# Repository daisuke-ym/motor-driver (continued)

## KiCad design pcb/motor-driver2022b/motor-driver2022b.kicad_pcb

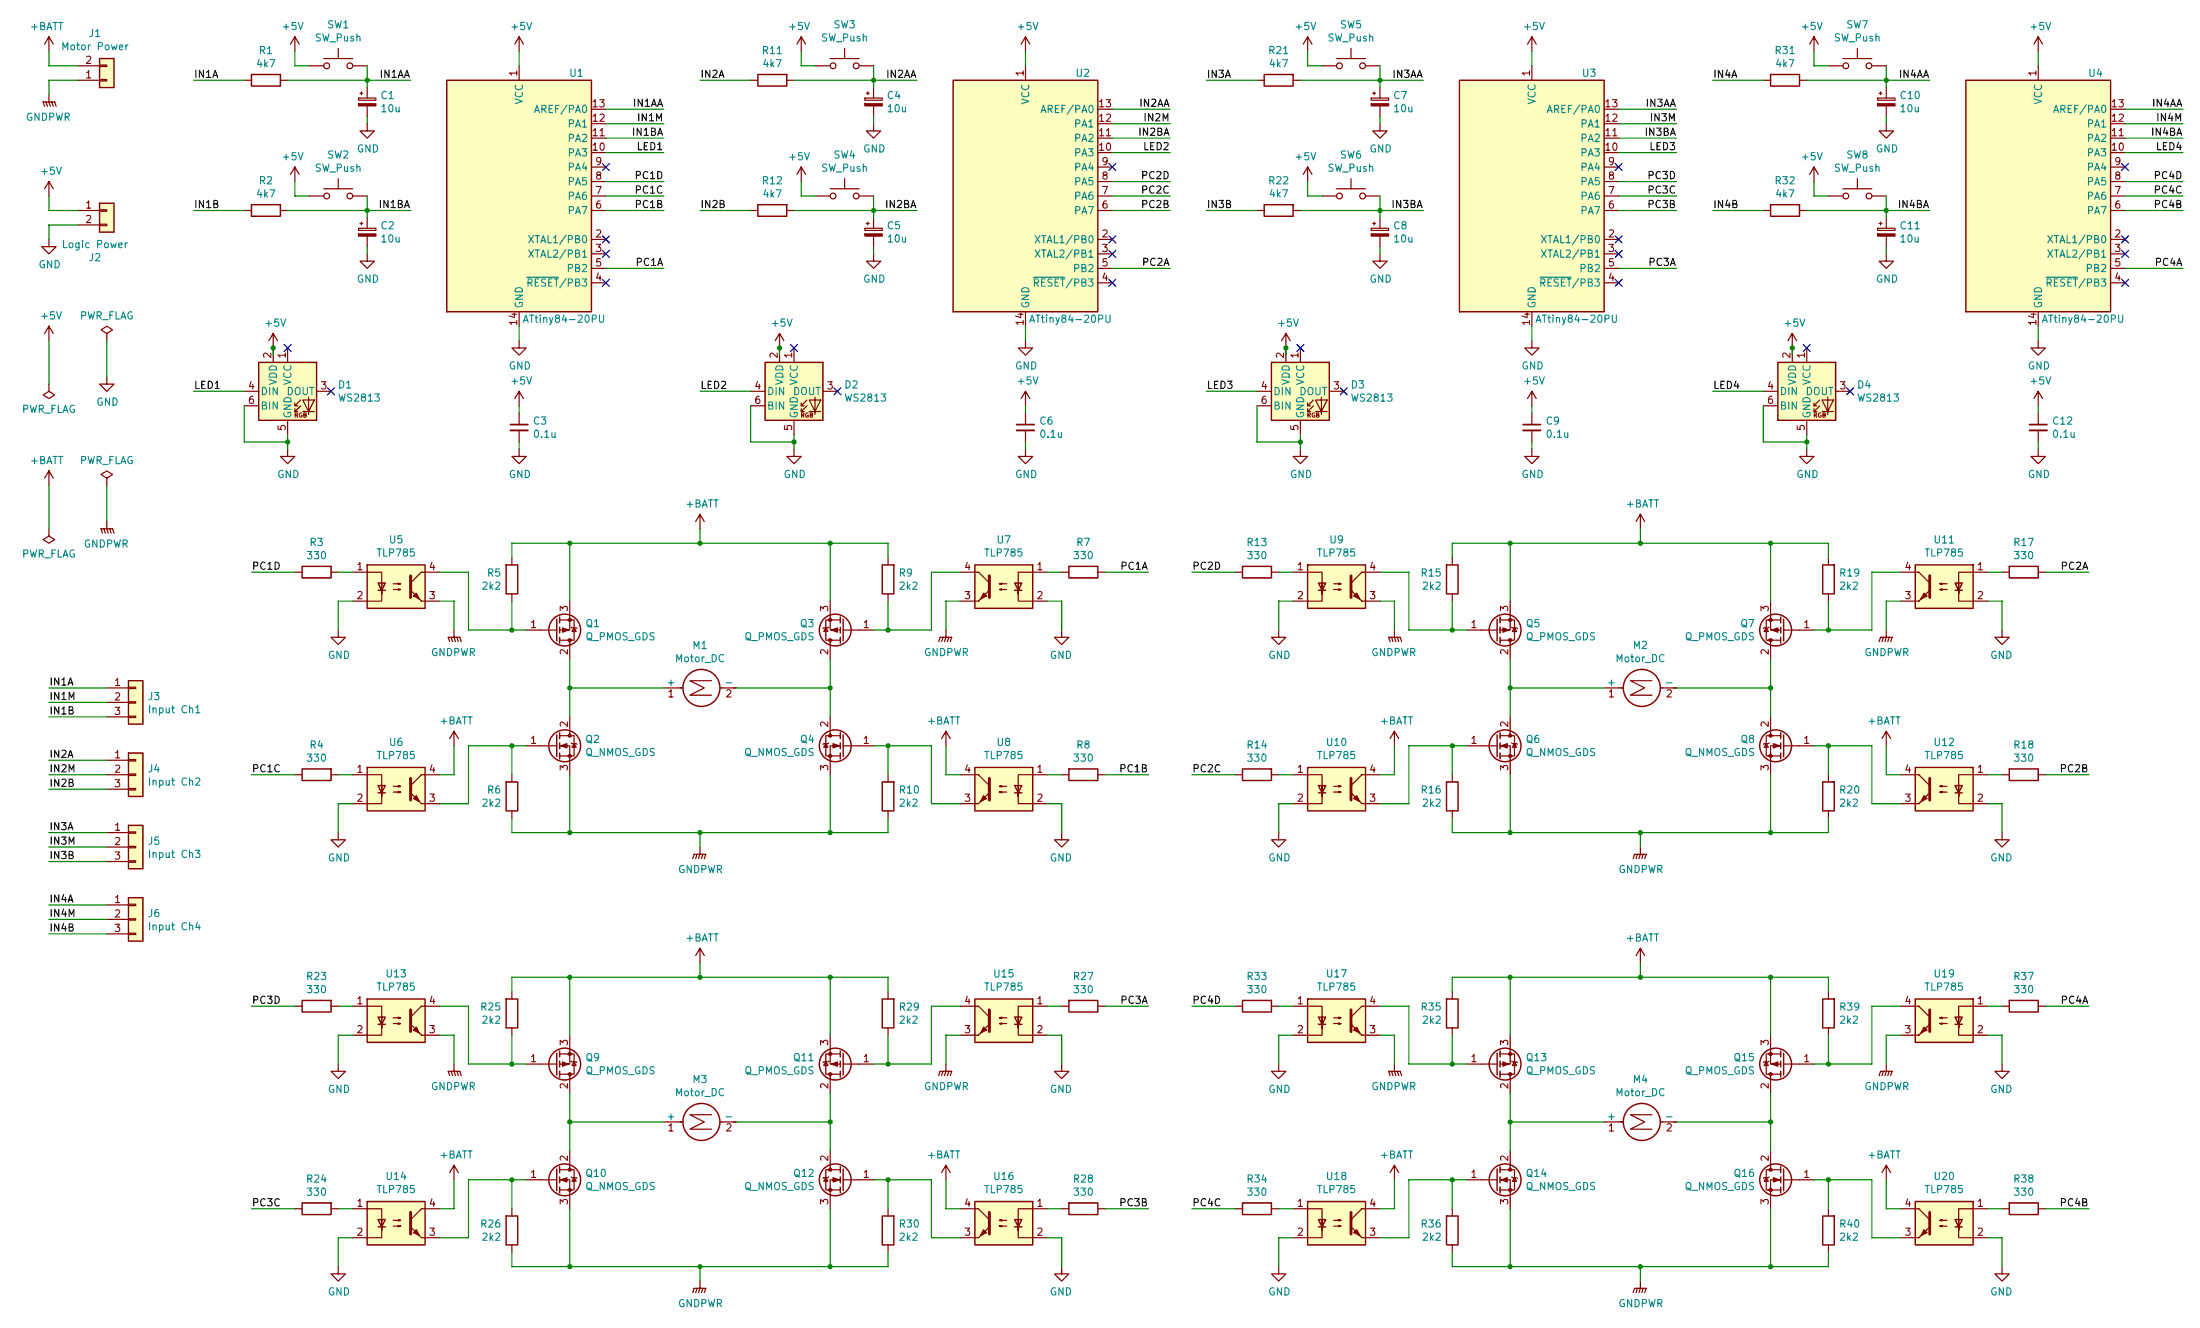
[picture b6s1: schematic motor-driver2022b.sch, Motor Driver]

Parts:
C1, C2, C4, C5, C7, C8, C10, C11: 10u; CP_Radial_D4.0mm_P1.50mm
C3, C6, C9, C12: 0.1u; C_Disc_D3.4mm_W2.1mm_P2.50mm
D1, D2, D3, D4: WS2813; LED_WS2812_PLCC6_5.0x5.0mm_P1.6mm
J1: Motor Power; AMASS_XT30PW-F_1x02_P2.50mm_Horizontal
J2: Logic Power; PinHeader_1x02_P2.54mm_Horizontal
J3: Input Ch1; PinHeader_1x03_P2.54mm_Horizontal
J4: Input Ch2; PinHeader_1x03_P2.54mm_Horizontal
J5: Input Ch3; PinHeader_1x03_P2.54mm_Horizontal
J6: Input Ch4; PinHeader_1x03_P2.54mm_Horizontal
M1, M2, M3, M4: Motor_DC; AMASS_XT30PW-F_1x02_P2.50mm_Horizontal
Q1, Q3, Q5, Q7, Q9, Q11, Q13, Q15: Q_PMOS_GDS; TO-220-3_Horizontal_TabDown
Q2, Q4, Q6, Q8, Q10, Q12, Q14, Q16: Q_NMOS_GDS; TO-220-3_Horizontal_TabDown
R1, R2, R11, R12, R21, R22, R31, R32: 4k7; R_Axial_DIN0207_L6.3mm_D2.5mm_P10.16mm_Horizontal
R3, R4, R7, R8, R13, R14, R17, R18, R23, R24, R27, R28, R33, R34, R37, R38: 330; R_Axial_DIN0207_L6.3mm_D2.5mm_P10.16mm_Horizontal
R5, R6, R9, R10, R15, R16, R19, R20, R25, R26, R29, R30, R35, R36, R39, R40: 2k2; R_Axial_DIN0207_L6.3mm_D2.5mm_P10.16mm_Horizontal
SW1, SW2, SW3, SW4, SW5, SW6, SW7, SW8: SW_Push; TactSW_TVBP06_3.5x6.0-ThroughHole
U1, U2, U3, U4: ATtiny84-20PU; DIP-14_W7.62mm
U5, U6, U7, U8, U9, U10, U11, U12, U13, U14, U15, U16, U17, U18, U19, U20: TLP785; DIP-4_W7.62mm

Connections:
+5V: C3.1, C6.1, C9.1, C12.1, D1.2 (VDD), D2.2 (VDD), D3.2 (VDD), D4.2 (VDD), J2.1, SW1.2, SW2.2, SW3.2, SW4.2, SW5.2, SW6.2, SW7.2, SW8.2, U1.1 (VCC), U2.1 (VCC), U3.1 (VCC), U4.1 (VCC)
+BATT: J1.2, Q1.3 (S), Q3.3 (S), Q5.3 (S), Q7.3 (S), Q9.3 (S), Q11.3 (S), Q13.3 (S), Q15.3 (S), R5.2, R9.2, R15.2, R19.2, R25.2, R29.2, R35.2, R39.2, U6.4, U8.4, U10.4, U12.4, U14.4, U16.4, U18.4, U20.4
/IN1A: J3.1, R1.1
/IN1AA: C1.1, R1.2, SW1.1, U1.13 (AREF/PA0)
/IN1B: J3.3, R2.1
/IN1BA: C2.1, R2.2, SW2.1, U1.11 (PA2)
/IN1M: J3.2, U1.12 (PA1)
/IN2A: J4.1, R11.1
/IN2AA: C4.1, R11.2, SW3.1, U2.13 (AREF/PA0)
/IN2B: J4.3, R12.1
/IN2BA: C5.1, R12.2, SW4.1, U2.11 (PA2)
/IN2M: J4.2, U2.12 (PA1)
/IN3A: J5.1, R21.1
/IN3AA: C7.1, R21.2, SW5.1, U3.13 (AREF/PA0)
/IN3B: J5.3, R22.1
/IN3BA: C8.1, R22.2, SW6.1, U3.11 (PA2)
/IN3M: J5.2, U3.12 (PA1)
/IN4A: J6.1, R31.1
/IN4AA: C10.1, R31.2, SW7.1, U4.13 (AREF/PA0)
/IN4B: J6.3, R32.1
/IN4BA: C11.1, R32.2, SW8.1, U4.11 (PA2)
/IN4M: J6.2, U4.12 (PA1)
/LED1: D1.4 (DIN), U1.10 (PA3)
/LED2: D2.4 (DIN), U2.10 (PA3)
/LED3: D3.4 (DIN), U3.10 (PA3)
/LED4: D4.4 (DIN), U4.10 (PA3)
/PC1A: R7.1, U1.5 (PB2)
/PC1B: R8.1, U1.6 (PA7)
/PC1C: R4.1, U1.7 (PA6)
/PC1D: R3.1, U1.8 (PA5)
/PC2A: R17.1, U2.5 (PB2)
/PC2B: R18.1, U2.6 (PA7)
/PC2C: R14.1, U2.7 (PA6)
/PC2D: R13.1, U2.8 (PA5)
/PC3A: R27.1, U3.5 (PB2)
/PC3B: R28.1, U3.6 (PA7)
/PC3C: R24.1, U3.7 (PA6)
/PC3D: R23.1, U3.8 (PA5)
/PC4A: R37.1, U4.5 (PB2)
/PC4B: R38.1, U4.6 (PA7)
/PC4C: R34.1, U4.7 (PA6)
/PC4D: R33.1, U4.8 (PA5)
GND: C1.2, C2.2, C3.2, C4.2, C5.2, C6.2, C7.2, C8.2, C9.2, C10.2, C11.2, C12.2, D1.5 (GND), D1.6 (BIN), D2.5 (GND), D2.6 (BIN), D3.5 (GND), D3.6 (BIN), D4.5 (GND), D4.6 (BIN), J2.2, U1.14 (GND), U2.14 (GND), U3.14 (GND), U4.14 (GND), U5.2, U6.2, U7.2, U8.2, U9.2, U10.2, U11.2, U12.2, U13.2, U14.2, U15.2, U16.2, U17.2, U18.2, U19.2, U20.2
GNDPWR: J1.1, Q2.3 (S), Q4.3 (S), Q6.3 (S), Q8.3 (S), Q10.3 (S), Q12.3 (S), Q14.3 (S), Q16.3 (S), R6.1, R10.1, R16.1, R20.1, R26.1, R30.1, R36.1, R40.1, U5.3, U7.3, U9.3, U11.3, U13.3, U15.3, U17.3, U19.3
unnamed: M1.1 (+), Q1.2 (D), Q2.2 (D)
unnamed: M1.2 (-), Q3.2 (D), Q4.2 (D)
unnamed: M2.1 (+), Q5.2 (D), Q6.2 (D)
unnamed: M2.2 (-), Q7.2 (D), Q8.2 (D)
unnamed: M3.1 (+), Q9.2 (D), Q10.2 (D)
unnamed: M3.2 (-), Q11.2 (D), Q12.2 (D)
unnamed: M4.1 (+), Q13.2 (D), Q14.2 (D)
unnamed: M4.2 (-), Q15.2 (D), Q16.2 (D)
unnamed: Q1.1 (G), R5.1, U5.4
unnamed: Q2.1 (G), R6.2, U6.3
unnamed: Q3.1 (G), R9.1, U7.4
unnamed: Q4.1 (G), R10.2, U8.3
unnamed: Q5.1 (G), R15.1, U9.4
unnamed: Q6.1 (G), R16.2, U10.3
unnamed: Q7.1 (G), R19.1, U11.4
unnamed: Q8.1 (G), R20.2, U12.3
unnamed: Q9.1 (G), R25.1, U13.4
unnamed: Q10.1 (G), R26.2, U14.3
unnamed: Q11.1 (G), R29.1, U15.4
unnamed: Q12.1 (G), R30.2, U16.3
unnamed: Q13.1 (G), R35.1, U17.4
unnamed: Q14.1 (G), R36.2, U18.3
unnamed: Q15.1 (G), R39.1, U19.4
unnamed: Q16.1 (G), R40.2, U20.3
unnamed: R3.2, U5.1
unnamed: R4.2, U6.1
unnamed: R7.2, U7.1
unnamed: R8.2, U8.1
unnamed: R13.2, U9.1
unnamed: R14.2, U10.1
unnamed: R17.2, U11.1
unnamed: R18.2, U12.1
unnamed: R23.2, U13.1
unnamed: R24.2, U14.1
unnamed: R27.2, U15.1
unnamed: R28.2, U16.1
unnamed: R33.2, U17.1
unnamed: R34.2, U18.1
unnamed: R37.2, U19.1
unnamed: R38.2, U20.1

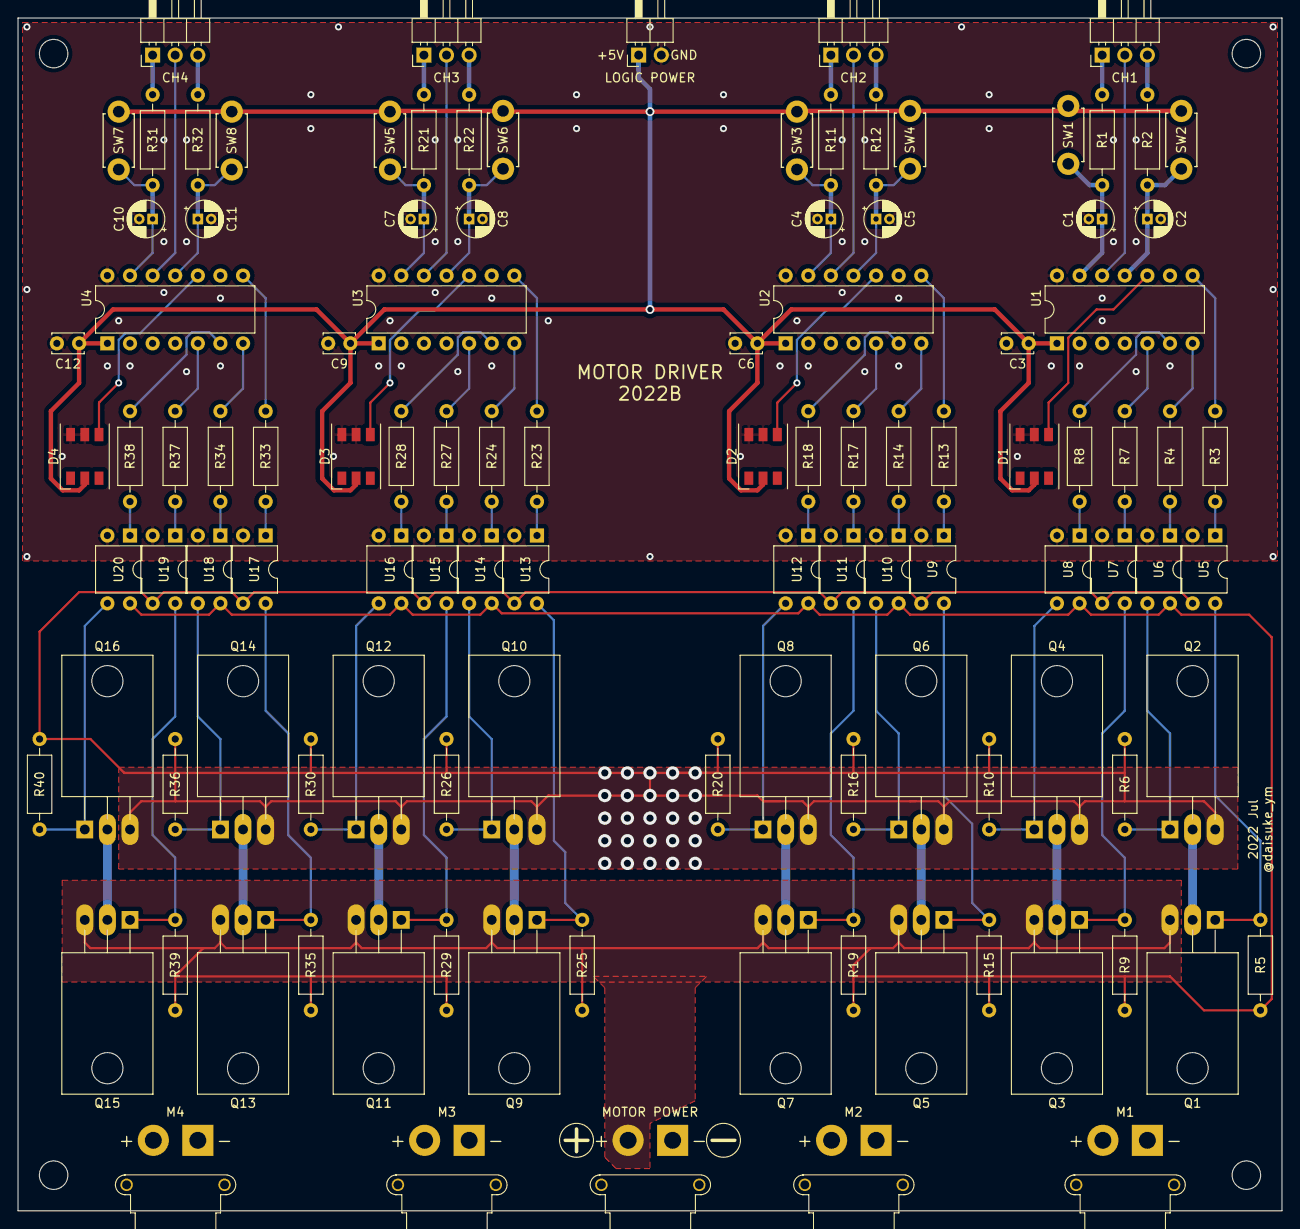
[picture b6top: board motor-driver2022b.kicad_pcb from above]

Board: 2 copper layers, 142.0 x 134.0 mm, 114 parts (0 on the bottom side), 84 nets.

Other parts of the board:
MH1, MH2, MH3, MH4: MountingHole_3.2mm_M3

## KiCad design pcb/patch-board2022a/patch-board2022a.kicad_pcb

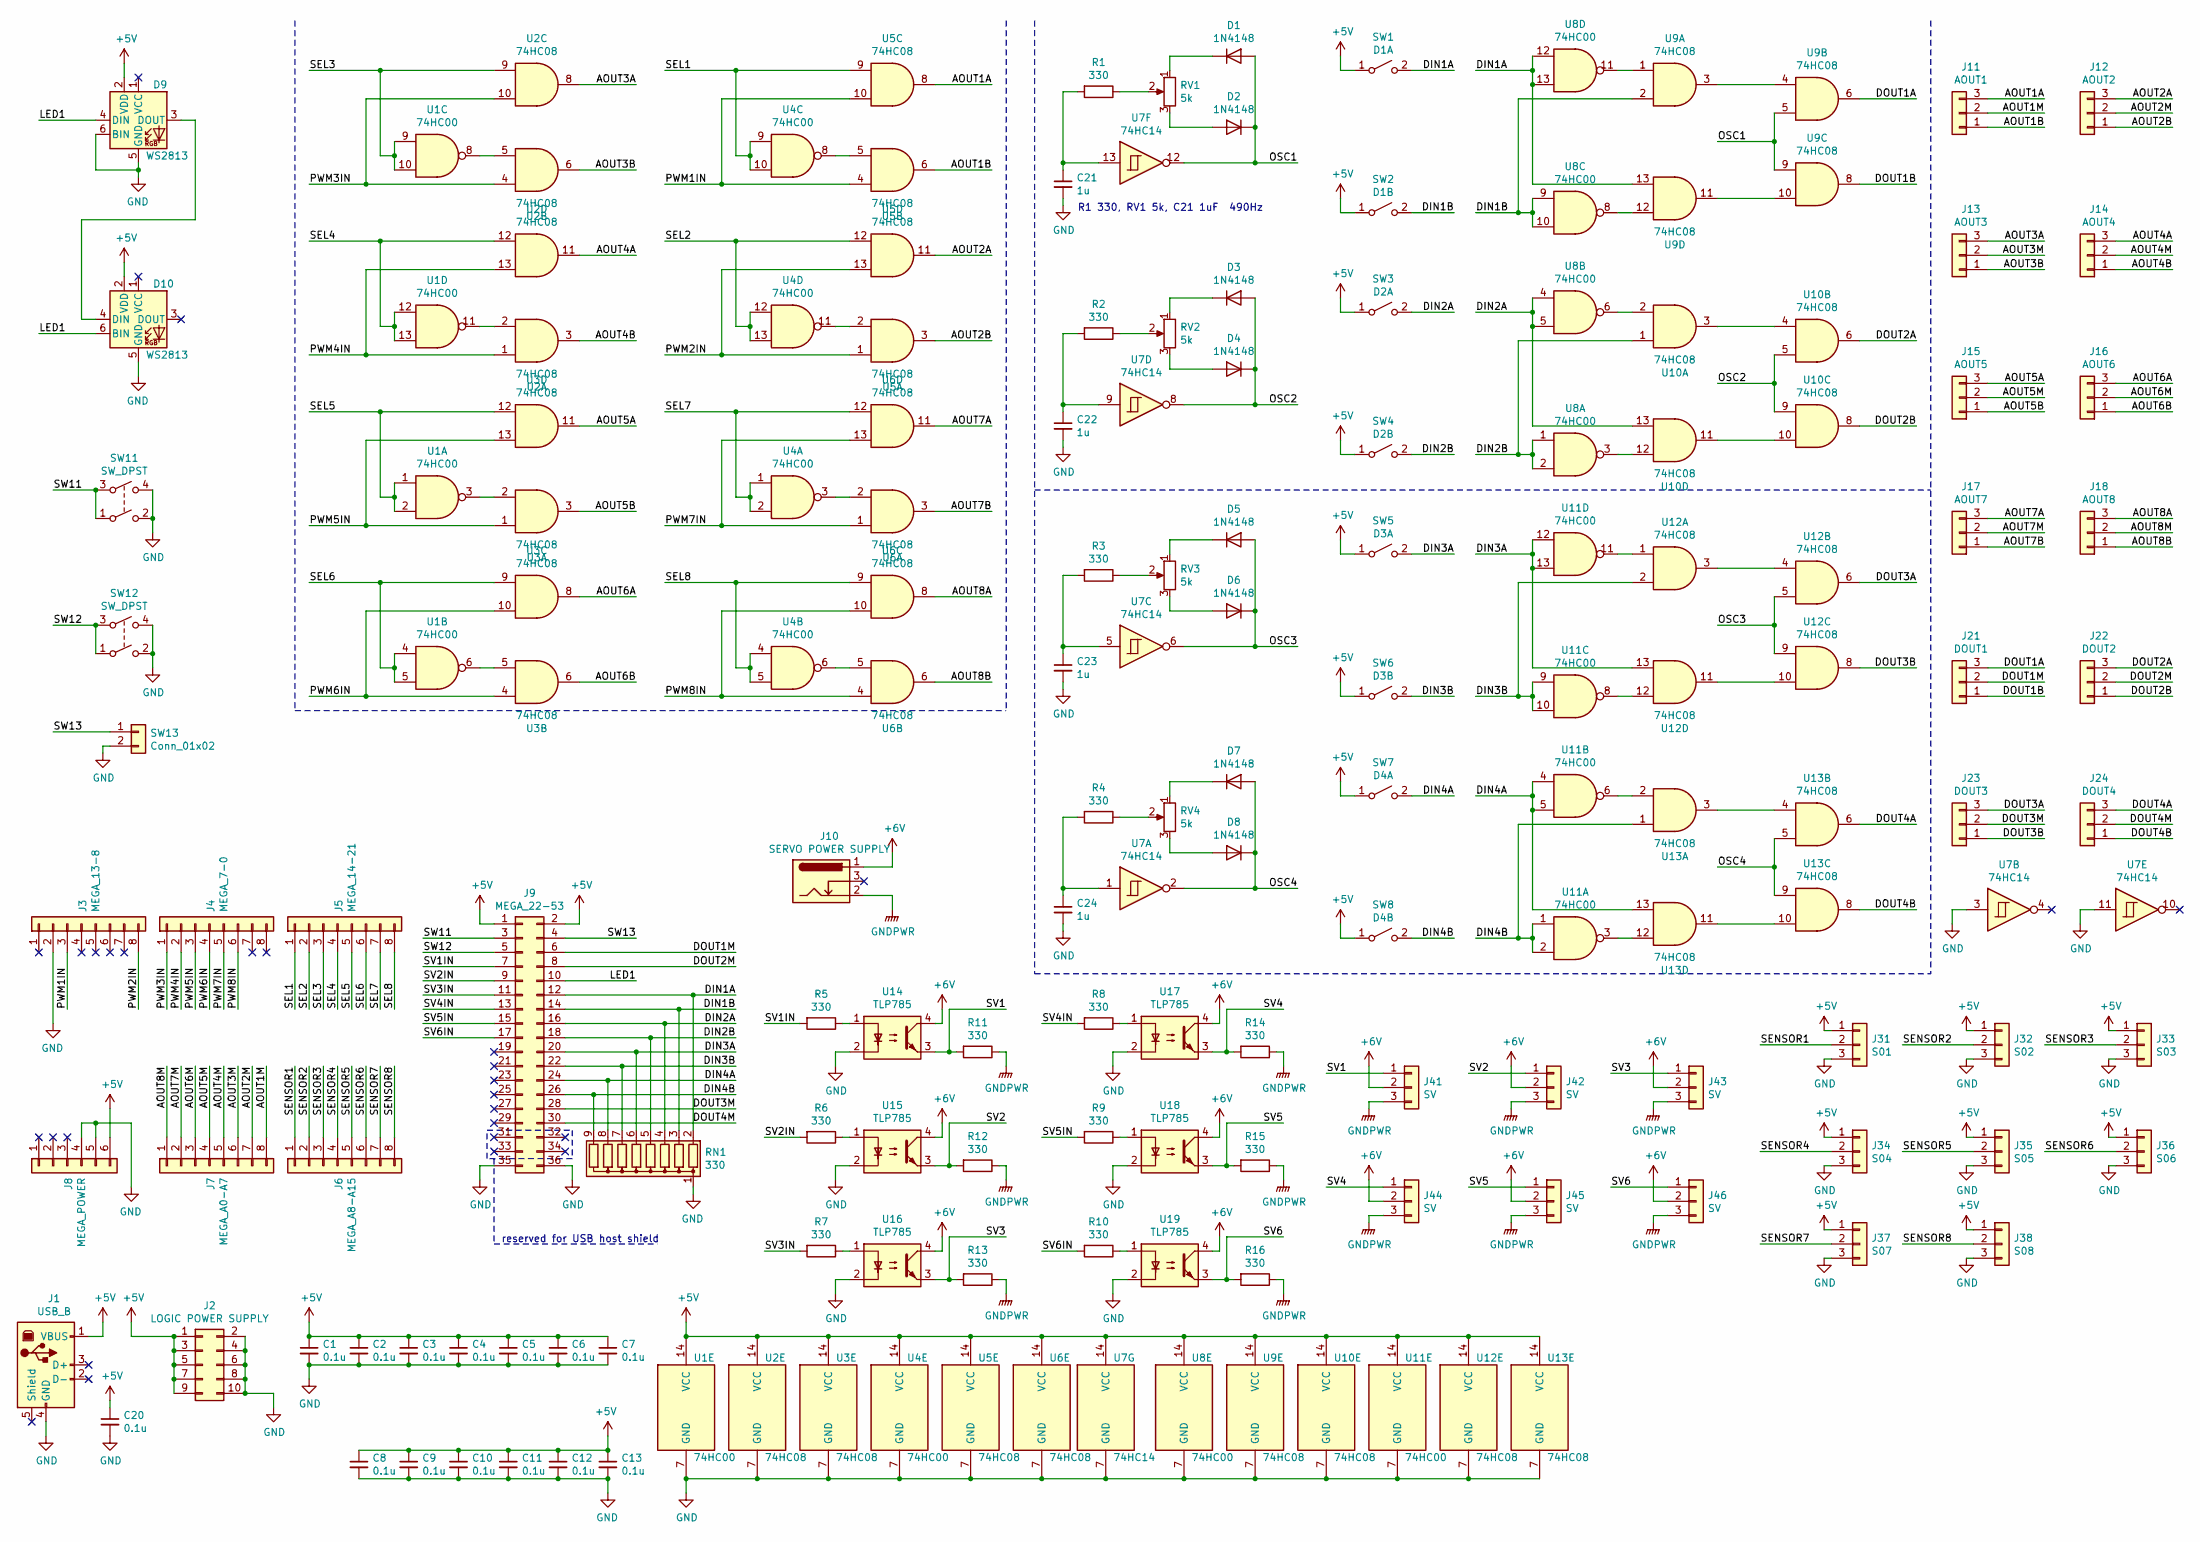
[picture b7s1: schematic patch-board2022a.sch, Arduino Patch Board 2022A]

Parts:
C1, C2, C3, C4, C5, C6, C7, C8, C9, C10, C11, C12, C13, C20: 0.1u; C_Disc_D3.4mm_W2.1mm_P2.50mm
C21, C22, C23, C24: 1u; C_Disc_D3.4mm_W2.1mm_P2.50mm
D1, D2, D3, D4, D5, D6, D7, D8: 1N4148; D_DO-35_SOD27_P7.62mm_Horizontal
D9, D10: WS2813; LED_WS2812_PLCC6_5.0x5.0mm_P1.6mm
J1: USB_B; USB_B_OST_USB-B1HSxx_Horizontal
J2: LOGIC POWER SUPPLY; PinHeader_2x05_P2.54mm_Vertical
J3: MEGA_13-8; PinHeader_1x08_P2.54mm_Vertical
J4: MEGA_7-0; PinHeader_1x08_P2.54mm_Vertical
J5: MEGA_14-21; PinHeader_1x08_P2.54mm_Vertical
J6: MEGA_A8-A15; PinHeader_1x08_P2.54mm_Vertical
J7: MEGA_A0-A7; PinHeader_1x08_P2.54mm_Vertical
J8: MEGA_POWER; PinHeader_1x06_P2.54mm_Vertical
J9: MEGA_22-53; PinHeader_2x18_P2.54mm_Vertical
J10: SERVO POWER SUPPLY; BarrelJack_Horizontal
J11: AOUT1; PinHeader_1x03_P2.54mm_Vertical
J12: AOUT2; PinHeader_1x03_P2.54mm_Vertical
J13: AOUT3; PinHeader_1x03_P2.54mm_Vertical
J14: AOUT4; PinHeader_1x03_P2.54mm_Vertical
J15: AOUT5; PinHeader_1x03_P2.54mm_Vertical
J16: AOUT6; PinHeader_1x03_P2.54mm_Vertical
J17: AOUT7; PinHeader_1x03_P2.54mm_Vertical
J18: AOUT8; PinHeader_1x03_P2.54mm_Vertical
J21: DOUT1; PinHeader_1x03_P2.54mm_Vertical
J22: DOUT2; PinHeader_1x03_P2.54mm_Vertical
J23: DOUT3; PinHeader_1x03_P2.54mm_Vertical
J24: DOUT4; PinHeader_1x03_P2.54mm_Vertical
J31: S01; PinHeader_1x03_P2.54mm_Vertical
J32: S02; PinHeader_1x03_P2.54mm_Vertical
J33: S03; PinHeader_1x03_P2.54mm_Vertical
J34: S04; PinHeader_1x03_P2.54mm_Vertical
J35: S05; PinHeader_1x03_P2.54mm_Vertical
J36: S06; PinHeader_1x03_P2.54mm_Vertical
J37: S07; PinHeader_1x03_P2.54mm_Vertical
J38: S08; PinHeader_1x03_P2.54mm_Vertical
J41, J42, J43, J44, J45, J46: SV; PinHeader_1x03_P2.54mm_Vertical
R1, R2, R3, R4, R5, R6, R7, R8, R9, R10, R11, R12, R13, R14, R15, R16: 330; R_Axial_DIN0207_L6.3mm_D2.5mm_P10.16mm_Horizontal
RN1: 330; R_Array_SIP9
RV1, RV2, RV3, RV4: 5k; GF063P1
SW1: D1A; TactSW_TVBP06_3.5x6.0-ThroughHole
SW2: D1B; TactSW_TVBP06_3.5x6.0-ThroughHole
SW3: D2A; TactSW_TVBP06_3.5x6.0-ThroughHole
SW4: D2B; TactSW_TVBP06_3.5x6.0-ThroughHole
SW5: D3A; TactSW_TVBP06_3.5x6.0-ThroughHole
SW6: D3B; TactSW_TVBP06_3.5x6.0-ThroughHole
SW7: D4A; TactSW_TVBP06_3.5x6.0-ThroughHole
SW8: D4B; TactSW_TVBP06_3.5x6.0-ThroughHole
SW11, SW12: SW_DPST; DTS-6-V-2
SW13: Conn_01x02; PinHeader_1x02_P2.54mm_Vertical
U1, U4, U8, U11: 74HC00; SO-14_5.3x10.2mm_P1.27mm
U2, U3, U5, U6, U9, U10, U12, U13: 74HC08; SO-14_5.3x10.2mm_P1.27mm
U7: 74HC14; SO-14_5.3x10.2mm_P1.27mm
U14, U15, U16, U17, U18, U19: TLP785; DIP-4_W7.62mm

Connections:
+5V: C1.1, C2.1, C3.1, C4.1, C5.1, C6.1, C7.1, C8.1, C9.1, C10.1, C11.1, C12.1, C13.1, C20.1, D9.2 (VDD), D10.2 (VDD), J1.1 (VBUS), J2.1, J2.3, J2.5, J2.7, J2.9, J8.6, J9.1, J9.2, J31.1, J32.1, J33.1, J34.1, J35.1, J36.1, J37.1, J38.1, SW1.1 (A), SW2.1 (A), SW3.1 (A), SW4.1 (A), SW5.1 (A), SW6.1 (A), SW7.1 (A), SW8.1 (A), U1.14 (VCC), U2.14 (VCC), U3.14 (VCC), U4.14 (VCC), U5.14 (VCC), U6.14 (VCC), U7.14 (VCC), U8.14 (VCC), U9.14 (VCC), U10.14 (VCC), U11.14 (VCC), U12.14 (VCC), U13.14 (VCC)
+6V: J10.1, J41.2, J42.2, J43.2, J44.2, J45.2, J46.2, U14.4, U15.4, U16.4, U17.4, U18.4, U19.4
/AOUT1A: J11.3, U5.8
/AOUT1B: J11.1, U5.6
/AOUT1M: J7.8, J11.2
/AOUT2A: J12.3, U5.11
/AOUT2B: J12.1, U5.3
/AOUT2M: J7.7, J12.2
/AOUT3A: J13.3, U2.8
/AOUT3B: J13.1, U2.6
/AOUT3M: J7.6, J13.2
/AOUT4A: J14.3, U2.11
/AOUT4B: J14.1, U2.3
/AOUT4M: J7.5, J14.2
/AOUT5A: J15.3, U3.11
/AOUT5B: J15.1, U3.3
/AOUT5M: J7.4, J15.2
/AOUT6A: J16.3, U3.8
/AOUT6B: J16.1, U3.6
/AOUT6M: J7.3, J16.2
/AOUT7A: J17.3, U6.11
/AOUT7B: J17.1, U6.3
/AOUT7M: J7.2, J17.2
/AOUT8A: J18.3, U6.8
/AOUT8B: J18.1, U6.6
/AOUT8M: J7.1, J18.2
/DIN1A: J9.12, RN1.2 (R1), SW1.2 (B), U8.12, U8.13, U9.13
/DIN1B: J9.14, RN1.3 (R2), SW2.2 (B), U8.9, U8.10, U9.2
/DIN2A: J9.16, RN1.4 (R3), SW3.2 (B), U8.4, U8.5, U10.13
/DIN2B: J9.18, RN1.5 (R4), SW4.2 (B), U8.1, U8.2, U10.1
/DIN3A: J9.20, RN1.6 (R5), SW5.2 (B), U11.12, U11.13, U12.13
/DIN3B: J9.22, RN1.7 (R6), SW6.2 (B), U11.9, U11.10, U12.2
/DIN4A: J9.24, RN1.8 (R7), SW7.2 (B), U11.4, U11.5, U13.13
/DIN4B: J9.26, RN1.9 (R8), SW8.2 (B), U11.1, U11.2, U13.1
/DOUT1A: J21.3, U9.6
/DOUT1B: J21.1, U9.8
/DOUT1M: J9.6, J21.2
/DOUT2A: J22.3, U10.6
/DOUT2B: J22.1, U10.8
/DOUT2M: J9.8, J22.2
/DOUT3A: J23.3, U12.6
/DOUT3B: J23.1, U12.8
/DOUT3M: J9.28, J23.2
/DOUT4A: J24.3, U13.6
/DOUT4B: J24.1, U13.8
/DOUT4M: J9.30, J24.2
/LED1: D9.4 (DIN), D10.6 (BIN), J9.10
/OSC1: D1.2 (A), D2.1 (K), U7.12, U9.5, U9.9
/OSC2: D3.2 (A), D4.1 (K), U7.8, U10.5, U10.9
/OSC3: D5.2 (A), D6.1 (K), U7.6, U12.5, U12.9
/OSC4: D7.2 (A), D8.1 (K), U7.2, U13.5, U13.9
/PWM1IN: J3.3, U5.4, U5.10
/PWM2IN: J3.8, U5.1, U5.13
/PWM3IN: J4.1, U2.4, U2.10
/PWM4IN: J4.2, U2.1, U2.13
/PWM5IN: J4.3, U3.1, U3.13
/PWM6IN: J4.4, U3.4, U3.10
/PWM7IN: J4.5, U6.1, U6.13
/PWM8IN: J4.6, U6.4, U6.10
/SEL1: J5.1, U4.9, U4.10, U5.9
/SEL2: J5.2, U4.12, U4.13, U5.12
/SEL3: J5.3, U1.9, U1.10, U2.9
/SEL4: J5.4, U1.12, U1.13, U2.12
/SEL5: J5.5, U1.1, U1.2, U3.12
/SEL6: J5.6, U1.4, U1.5, U3.9
/SEL7: J5.7, U4.1, U4.2, U6.12
/SEL8: J5.8, U4.4, U4.5, U6.9
/SENSOR1: J6.1, J31.2
/SENSOR2: J6.2, J32.2
/SENSOR3: J6.3, J33.2
/SENSOR4: J6.4, J34.2
/SENSOR5: J6.5, J35.2
/SENSOR6: J6.6, J36.2
/SENSOR7: J6.7, J37.2
/SENSOR8: J6.8, J38.2
/SV1: J41.1, R11.2, U14.3
/SV1IN: J9.7, R5.2
/SV2: J42.1, R12.2, U15.3
/SV2IN: J9.9, R6.2
/SV3: J43.1, R13.2, U16.3
/SV3IN: J9.11, R7.2
/SV4: J44.1, R14.2, U17.3
/SV4IN: J9.13, R8.2
/SV5: J45.1, R15.2, U18.3
/SV5IN: J9.15, R9.2
/SV6: J46.1, R16.2, U19.3
/SV6IN: J9.17, R10.2
/SW11: J9.3, SW11.1, SW11.3
/SW12: J9.5, SW12.1, SW12.3
/SW13: J9.4, SW13.1
GND: C1.2, C2.2, C3.2, C4.2, C5.2, C6.2, C7.2, C8.2, C9.2, C10.2, C11.2, C12.2, C13.2, C20.2, C21.2, C22.2, C23.2, C24.2, D9.5 (GND), D9.6 (BIN), D10.5 (GND), J1.4 (GND), J2.2, J2.4, J2.6, J2.8, J2.10, J3.2, J8.4, J8.5, J9.35, J9.36, J31.3, J32.3, J33.3, J34.3, J35.3, J36.3, J37.3, J38.3, RN1.1 (common), SW11.2, SW11.4, SW12.2, SW12.4, SW13.2, U1.7 (GND), U2.7 (GND), U3.7 (GND), U4.7 (GND), U5.7 (GND), U6.7 (GND), U7.3, U7.7 (GND), U7.11, U8.7 (GND), U9.7 (GND), U10.7 (GND), U11.7 (GND), U12.7 (GND), U13.7 (GND), U14.2, U15.2, U16.2, U17.2, U18.2, U19.2
GNDPWR: J10.2, J41.3, J42.3, J43.3, J44.3, J45.3, J46.3, R11.1, R12.1, R13.1, R14.1, R15.1, R16.1
unnamed: C21.1, R1.2, U7.13
unnamed: C22.1, R2.2, U7.9
unnamed: C23.1, R3.2, U7.5
unnamed: C24.1, R4.2, U7.1
unnamed: D1.1 (K), RV1.1
unnamed: D2.2 (A), RV1.3
unnamed: D3.1 (K), RV2.1
unnamed: D4.2 (A), RV2.3
unnamed: D5.1 (K), RV3.1
unnamed: D6.2 (A), RV3.3
unnamed: D7.1 (K), RV4.1
unnamed: D8.2 (A), RV4.3
unnamed: D9.3 (DOUT), D10.4 (DIN)
unnamed: R1.1, RV1.2
unnamed: R2.1, RV2.2
unnamed: R3.1, RV3.2
unnamed: R4.1, RV4.2
unnamed: R5.1, U14.1
unnamed: R6.1, U15.1
unnamed: R7.1, U16.1
unnamed: R8.1, U17.1
unnamed: R9.1, U18.1
unnamed: R10.1, U19.1
unnamed: U1.3, U3.2
unnamed: U1.6, U3.5
unnamed: U1.8, U2.5
unnamed: U1.11, U2.2
unnamed: U4.3, U6.2
unnamed: U4.6, U6.5
unnamed: U4.8, U5.5
unnamed: U4.11, U5.2
unnamed: U8.8, U9.12
unnamed: U8.11, U9.1
unnamed: U9.3, U9.4
unnamed: U9.10, U9.11
unnamed: U8.6, U10.2
unnamed: U10.3, U10.4
unnamed: U10.10, U10.11
unnamed: U8.3, U10.12
unnamed: U11.3, U13.12
unnamed: U11.6, U13.2
unnamed: U11.8, U12.12
unnamed: U11.11, U12.1
unnamed: U12.3, U12.4
unnamed: U12.10, U12.11
unnamed: U13.3, U13.4
unnamed: U13.10, U13.11

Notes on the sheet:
R1 330, RV1 5k, C21 1uF 490Hz
reserved for USB host shield

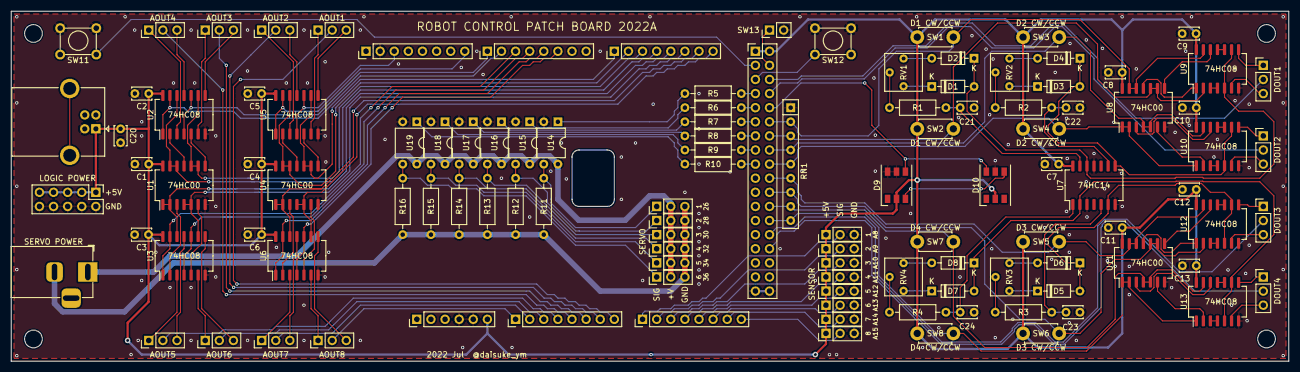
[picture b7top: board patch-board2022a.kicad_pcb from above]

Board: 2 copper layers, 230.0 x 63.0 mm, 115 parts (0 on the bottom side), 139 nets.

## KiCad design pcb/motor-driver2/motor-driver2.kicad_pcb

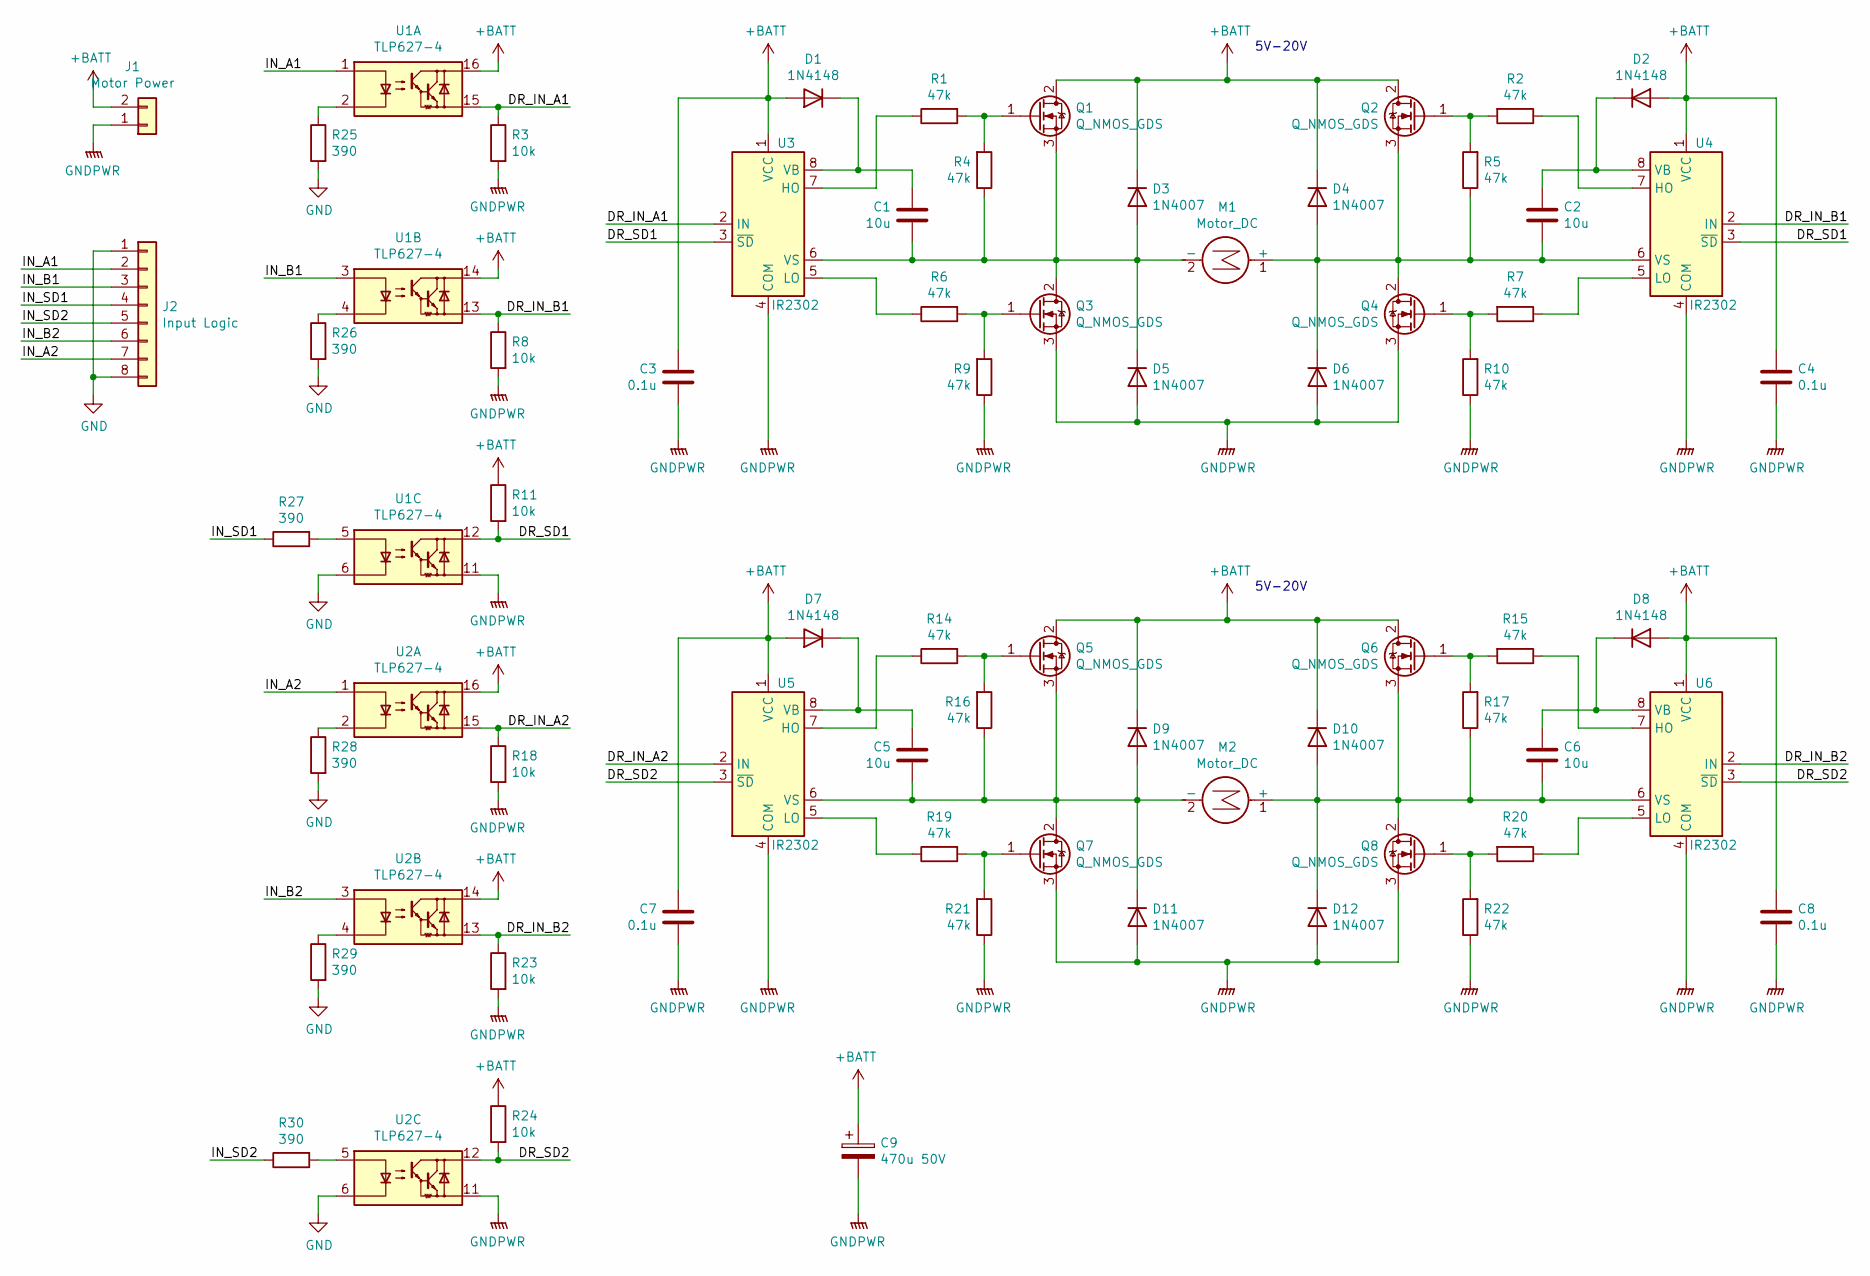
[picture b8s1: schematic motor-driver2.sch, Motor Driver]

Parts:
C1, C2, C5, C6: 10u; C_Disc_D6.0mm_W4.4mm_P5.00mm
C3, C4, C7, C8: 0.1u; C_Disc_D5.0mm_W2.5mm_P2.50mm
C9: 470u 50V; CP_Radial_D12.5mm_P5.00mm
D1, D2, D7, D8: 1N4148; D_DO-35_SOD27_P2.54mm_Vertical_KathodeUp
D3, D4, D5, D6, D9, D10, D11, D12: 1N4007; D_DO-41_SOD81_P2.54mm_Vertical_KathodeUp
J1: Motor Power; JST_VH_B2P-VH_1x02_P3.96mm_Vertical
J2: Input Logic; PinHeader_1x08_P2.54mm_Vertical
M1, M2: Motor_DC; JST_VH_B2P-VH_1x02_P3.96mm_Vertical
Q1, Q2, Q3, Q4, Q5, Q6, Q7, Q8: Q_NMOS_GDS; TO-220-3_Vertical
R1, R2, R4, R5, R6, R7, R9, R10, R14, R15, R16, R17, R19, R20, R21, R22: 47k; R_Axial_DIN0207_L6.3mm_D2.5mm_P2.54mm_Vertical
R3, R8, R11, R18, R23, R24: 10k; R_Axial_DIN0207_L6.3mm_D2.5mm_P2.54mm_Vertical
R25, R26, R27, R28, R29, R30: 390; R_Axial_DIN0207_L6.3mm_D2.5mm_P2.54mm_Vertical
U1, U2: TLP627-4; DIP-16_W7.62mm
U3, U4, U5, U6: IR2302; DIP-8_W7.62mm

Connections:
+BATT: C3.1, C4.1, C7.1, C8.1, C9.1, D1.2 (A), D2.2 (A), D3.1 (K), D4.1 (K), D7.2 (A), D8.2 (A), D9.1 (K), D10.1 (K), J1.2, Q1.2 (D), Q2.2 (D), Q5.2 (D), Q6.2 (D), R11.1, R24.1, U1.14, U1.16, U2.14, U2.16, U3.1 (VCC), U4.1 (VCC), U5.1 (VCC), U6.1 (VCC)
/DR_IN_A1: R3.1, U1.15, U3.2 (IN)
/DR_IN_A2: R18.1, U2.15, U5.2 (IN)
/DR_IN_B1: R8.1, U1.13, U4.2 (IN)
/DR_IN_B2: R23.1, U2.13, U6.2 (IN)
/DR_SD1: R11.2, U1.12, U3.3 (~SD), U4.3 (~SD)
/DR_SD2: R24.2, U2.12, U5.3 (~SD), U6.3 (~SD)
/IN_A1: J2.2, U1.1
/IN_A2: J2.7, U2.1
/IN_B1: J2.3, U1.3
/IN_B2: J2.6, U2.3
/IN_SD1: J2.4, R27.1
/IN_SD2: J2.5, R30.1
GND: J2.1, J2.8, R25.2, R26.2, R28.2, R29.2, U1.6, U2.6
GNDPWR: C3.2, C4.2, C7.2, C8.2, C9.2, D5.2 (A), D6.2 (A), D11.2 (A), D12.2 (A), J1.1, Q3.3 (S), Q4.3 (S), Q7.3 (S), Q8.3 (S), R3.2, R8.2, R9.1, R10.1, R18.2, R21.1, R22.1, R23.2, U1.11, U2.11, U3.4 (COM), U4.4 (COM), U5.4 (COM), U6.4 (COM)
unnamed: C1.1, D1.1 (K), U3.8 (VB)
unnamed: C1.2, D3.2 (A), D5.1 (K), M1.2 (-), Q1.3 (S), Q3.2 (D), R4.1, U3.6 (VS)
unnamed: C2.1, D2.1 (K), U4.8 (VB)
unnamed: C2.2, D4.2 (A), D6.1 (K), M1.1 (+), Q2.3 (S), Q4.2 (D), R5.1, U4.6 (VS)
unnamed: C5.1, D7.1 (K), U5.8 (VB)
unnamed: C5.2, D9.2 (A), D11.1 (K), M2.2 (-), Q5.3 (S), Q7.2 (D), R16.1, U5.6 (VS)
unnamed: C6.1, D8.1 (K), U6.8 (VB)
unnamed: C6.2, D10.2 (A), D12.1 (K), M2.1 (+), Q6.3 (S), Q8.2 (D), R17.1, U6.6 (VS)
unnamed: Q1.1 (G), R1.2, R4.2
unnamed: Q2.1 (G), R2.2, R5.2
unnamed: Q3.1 (G), R6.2, R9.2
unnamed: Q4.1 (G), R7.2, R10.2
unnamed: Q5.1 (G), R14.2, R16.2
unnamed: Q6.1 (G), R15.2, R17.2
unnamed: Q7.1 (G), R19.2, R21.2
unnamed: Q8.1 (G), R20.2, R22.2
unnamed: R1.1, U3.7 (HO)
unnamed: R2.1, U4.7 (HO)
unnamed: R6.1, U3.5 (LO)
unnamed: R7.1, U4.5 (LO)
unnamed: R14.1, U5.7 (HO)
unnamed: R15.1, U6.7 (HO)
unnamed: R19.1, U5.5 (LO)
unnamed: R20.1, U6.5 (LO)
unnamed: R25.1, U1.2
unnamed: R26.1, U1.4
unnamed: R27.2, U1.5
unnamed: R28.1, U2.2
unnamed: R29.1, U2.4
unnamed: R30.2, U2.5

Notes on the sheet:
5V-20V

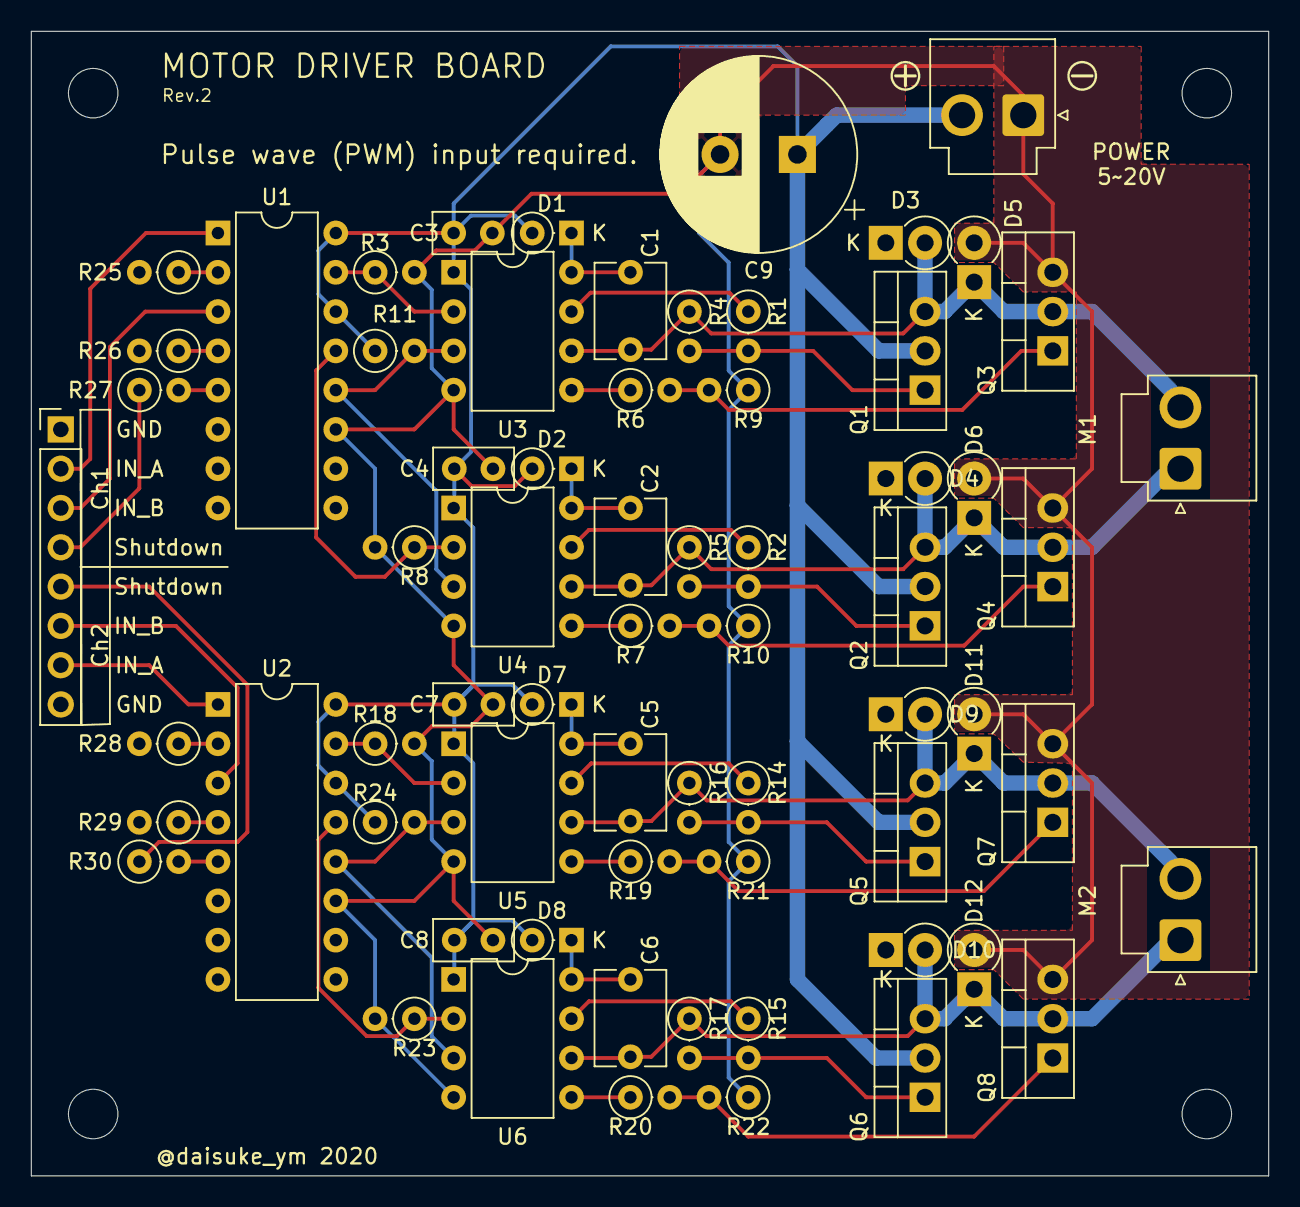
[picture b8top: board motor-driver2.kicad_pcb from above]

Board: 2 copper layers, 80.0 x 74.0 mm, 71 parts (0 on the bottom side), 45 nets.

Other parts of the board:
MH1, MH2, MH3, MH4: MountingHole_3.2mm_M3

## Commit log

2020-08-07 初期フォルダを追加
2020-08-07 基板データを追加
2020-08-31 フォルダを追加
2020-08-31 ファイルを移動
2020-09-04 モータードライバ基板の補助基板の設計データを追加 まだ配線経路を見直す必要あり
2020-09-07 基板データ完成
2020-09-22 コネクタを変更
2020-09-22 フォトカプラを削除 基板レイアウトを大幅変更 コネクタはすべて横出しにした
2020-10-28 ラインセンサ基板データを追加
2021-07-25 4chモータドライバ基板 未完成
2021-07-25 2chモータドライバ基板
2021-07-26 ほぼ完成
2021-07-26 登録するファイルを間違えた
2021-07-26 一応完成
2021-07-27 壁センサ基板完成
2021-07-28 電源ラインが細かったので，基板サイズを大きくして太く修正した。
2021-07-28 コンデンサのフットプリントを変更した
2021-07-28 ロボットコントローラのパッチボード（Arduino MEGAのシールド形式）
2021-07-29 まだ途中
2021-07-30 ガーバーデータを追加
2021-07-30 アートワーク完成 ガーバーデータ追加
2021-07-31 スケッチ保存用フォルダを追加
2021-08-04 Arduino MEGA に接続するピンヘッダの配置を分かりやすくした
2021-08-06 MotorDriver-4 および MotorDriver-5 用の制御プログラム
2021-08-19 PS3 コントローラで patch-board の動作テストをするスケッチ
2021-08-20 D13 ピンの配線ミスを修正 AOUT5-8 のシルクミスを修正 U13 のユニット割り当てミスを修正
2021-08-24 とりあえず動くようにしたサンプルを上げておく
2021-12-06 motor-driver-4基板 および motor-driver-5基板用ファームウェア
2022-07-08 2022年度版モータドライバを追加
    2021年度からの変更点
    ATtiny85 -> ATtiny84
    Input 2pin -> 3pin
    LED追加
    Output VH -> XT
2022-07-08 2022年度版モータドライバを追加 （4ch）
    2021年度からの変更点
    ATtiny85 -> ATtiny84
    Input 2pin -> 3pin
    LED追加
    Output VH -> XT
2022-07-08 2022年度版モータドライバを追加
    2021年度からの変更点
    ブレーキが利くようにした
2022-07-08 2022年度版物体センサ基板を追加
2022-07-08 2022年度版パッチボードを追加 （未完成）
2022-07-11 シルクが間違っていたのを修正
2022-07-11 2022年度版パッチボードBを追加
2022-07-13 ビアのサイズを変更 ビアを追加
2022-08-17 motor_driver_firmからRESETピンを殺すことでブレーキをかけるようにしたもの
2022-08-17 2022年版ドライバ用ファームウェア 制御入力にモード切替を追加し，ブレーキモードとフリーモードの切り替えをできるようにした。
2022-08-17 ピン番号の割り当てが間違っていたのを修正
2022-08-25 2022年度版コントローラプログラムを追加
2022-08-28 コントローラ切断時に，アナログチャネル5-8を停止するようにした。
2022-10-06 LEDが明るすぎたので，暗くした。 VSCode用のファイルを追加した
2022-10-06 PatchBoard2022B 用の動作確認プログラムを追加
2022-10-07 動作テスト2
2022-10-10 とりあえず動くようになったので,コミットしておく。
2022-10-12 メカナムの移動方向を調整する関数を追加（未使用）
2022-10-15 待機時，SW12でメカナム調整モードに入るコードを追加した
2023-08-22 2022年度版の制御プログラム
2023-08-25 2023年版ロボット制御プログラム（ラジコン型）
2023-08-25 2023年版ロボット制御プログラム（自立型）初期バージョン
2024-06-23 面付けデータを修正
2024-08-29 trunk 内のファイルをルートに移動
2024-08-30 デュアルMOSFET TPC8408(N-ch + P-ch)を2個使ったHブリッジ基板を作った。 74HC00を使った貫通電流防止ロジックあり。 デッドタイムはコントローラ側で実装すること。
2024-09-20 配線が間違っていたのを修正した
2026-04-25 2026年版モータードライバー基板データを追加
